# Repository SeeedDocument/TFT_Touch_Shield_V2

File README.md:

# 2.8TFT Touch Shield
---
SKU: 104030004

Wiki Link: [wiki.seeed.cc](wiki.seeed.cc)

Change Log:

- 2016-11-7: create repos by Jeremy (Jeremy.xiao@seeed.cc)

## About Seeed

Seeed is a hardware innovation platform for makers to grow inspirations into differentiating products. By working closely with technology providers of all scale, Seeed provides accessible technologies with quality, speed and supply chain knowledge. When prototypes are ready to iterate, Seeed helps productize 1 to 1,000 pcs using in-house engineering, supply chain management and agile manufacture forces. Seeed also team up with incubators, Chinese tech ecosystem, investors and distribution channels to portal Maker startups beyond.

## Contribution

We warmly welcome contribution to this documentation project. You can do this basically by [forking](https://help.github.com/articles/fork-a-repo), committing modifications and then [pulling requests](https://help.github.com/articles/using-pull-requests) (follow the links above for operating guide). Adding change log and your contact into file header is encouraged. Thanks for your contribution.

LICENSE
-------
Copyright (c) 2008-2016 Seeed Development Limited (www.seeedstudio.com / www.seeed.cc)

### Documents and Images
</a><br />
This work (product documents and associated images) are licensed under a <a rel="license" href="http://creativecommons.org/licenses/by-sa/4.0/">Creative Commons Attribution-ShareAlike 4.0 International License</a>. 

### Software Library
All demo software, code examples embedded in the document and any software libraray provided with the product document are licensed under [MIT License](https://github.com/SeeedDoc/WikiMigrationSync/blob/master/MIT_LICENSE "MIT LICENSE") unless otherwise specified.

### Thirdparty content
The resources provided with the product documents also contains datasheets, software examples and other content copyrighted by 3rd party authors and companies. All such items are copyright of respective owners. The use of such items are governed by their respective licenses.

All trademarks are the property of their respective owners.

### To Contact

Write to us at  with subject line "Wiki". Thanks

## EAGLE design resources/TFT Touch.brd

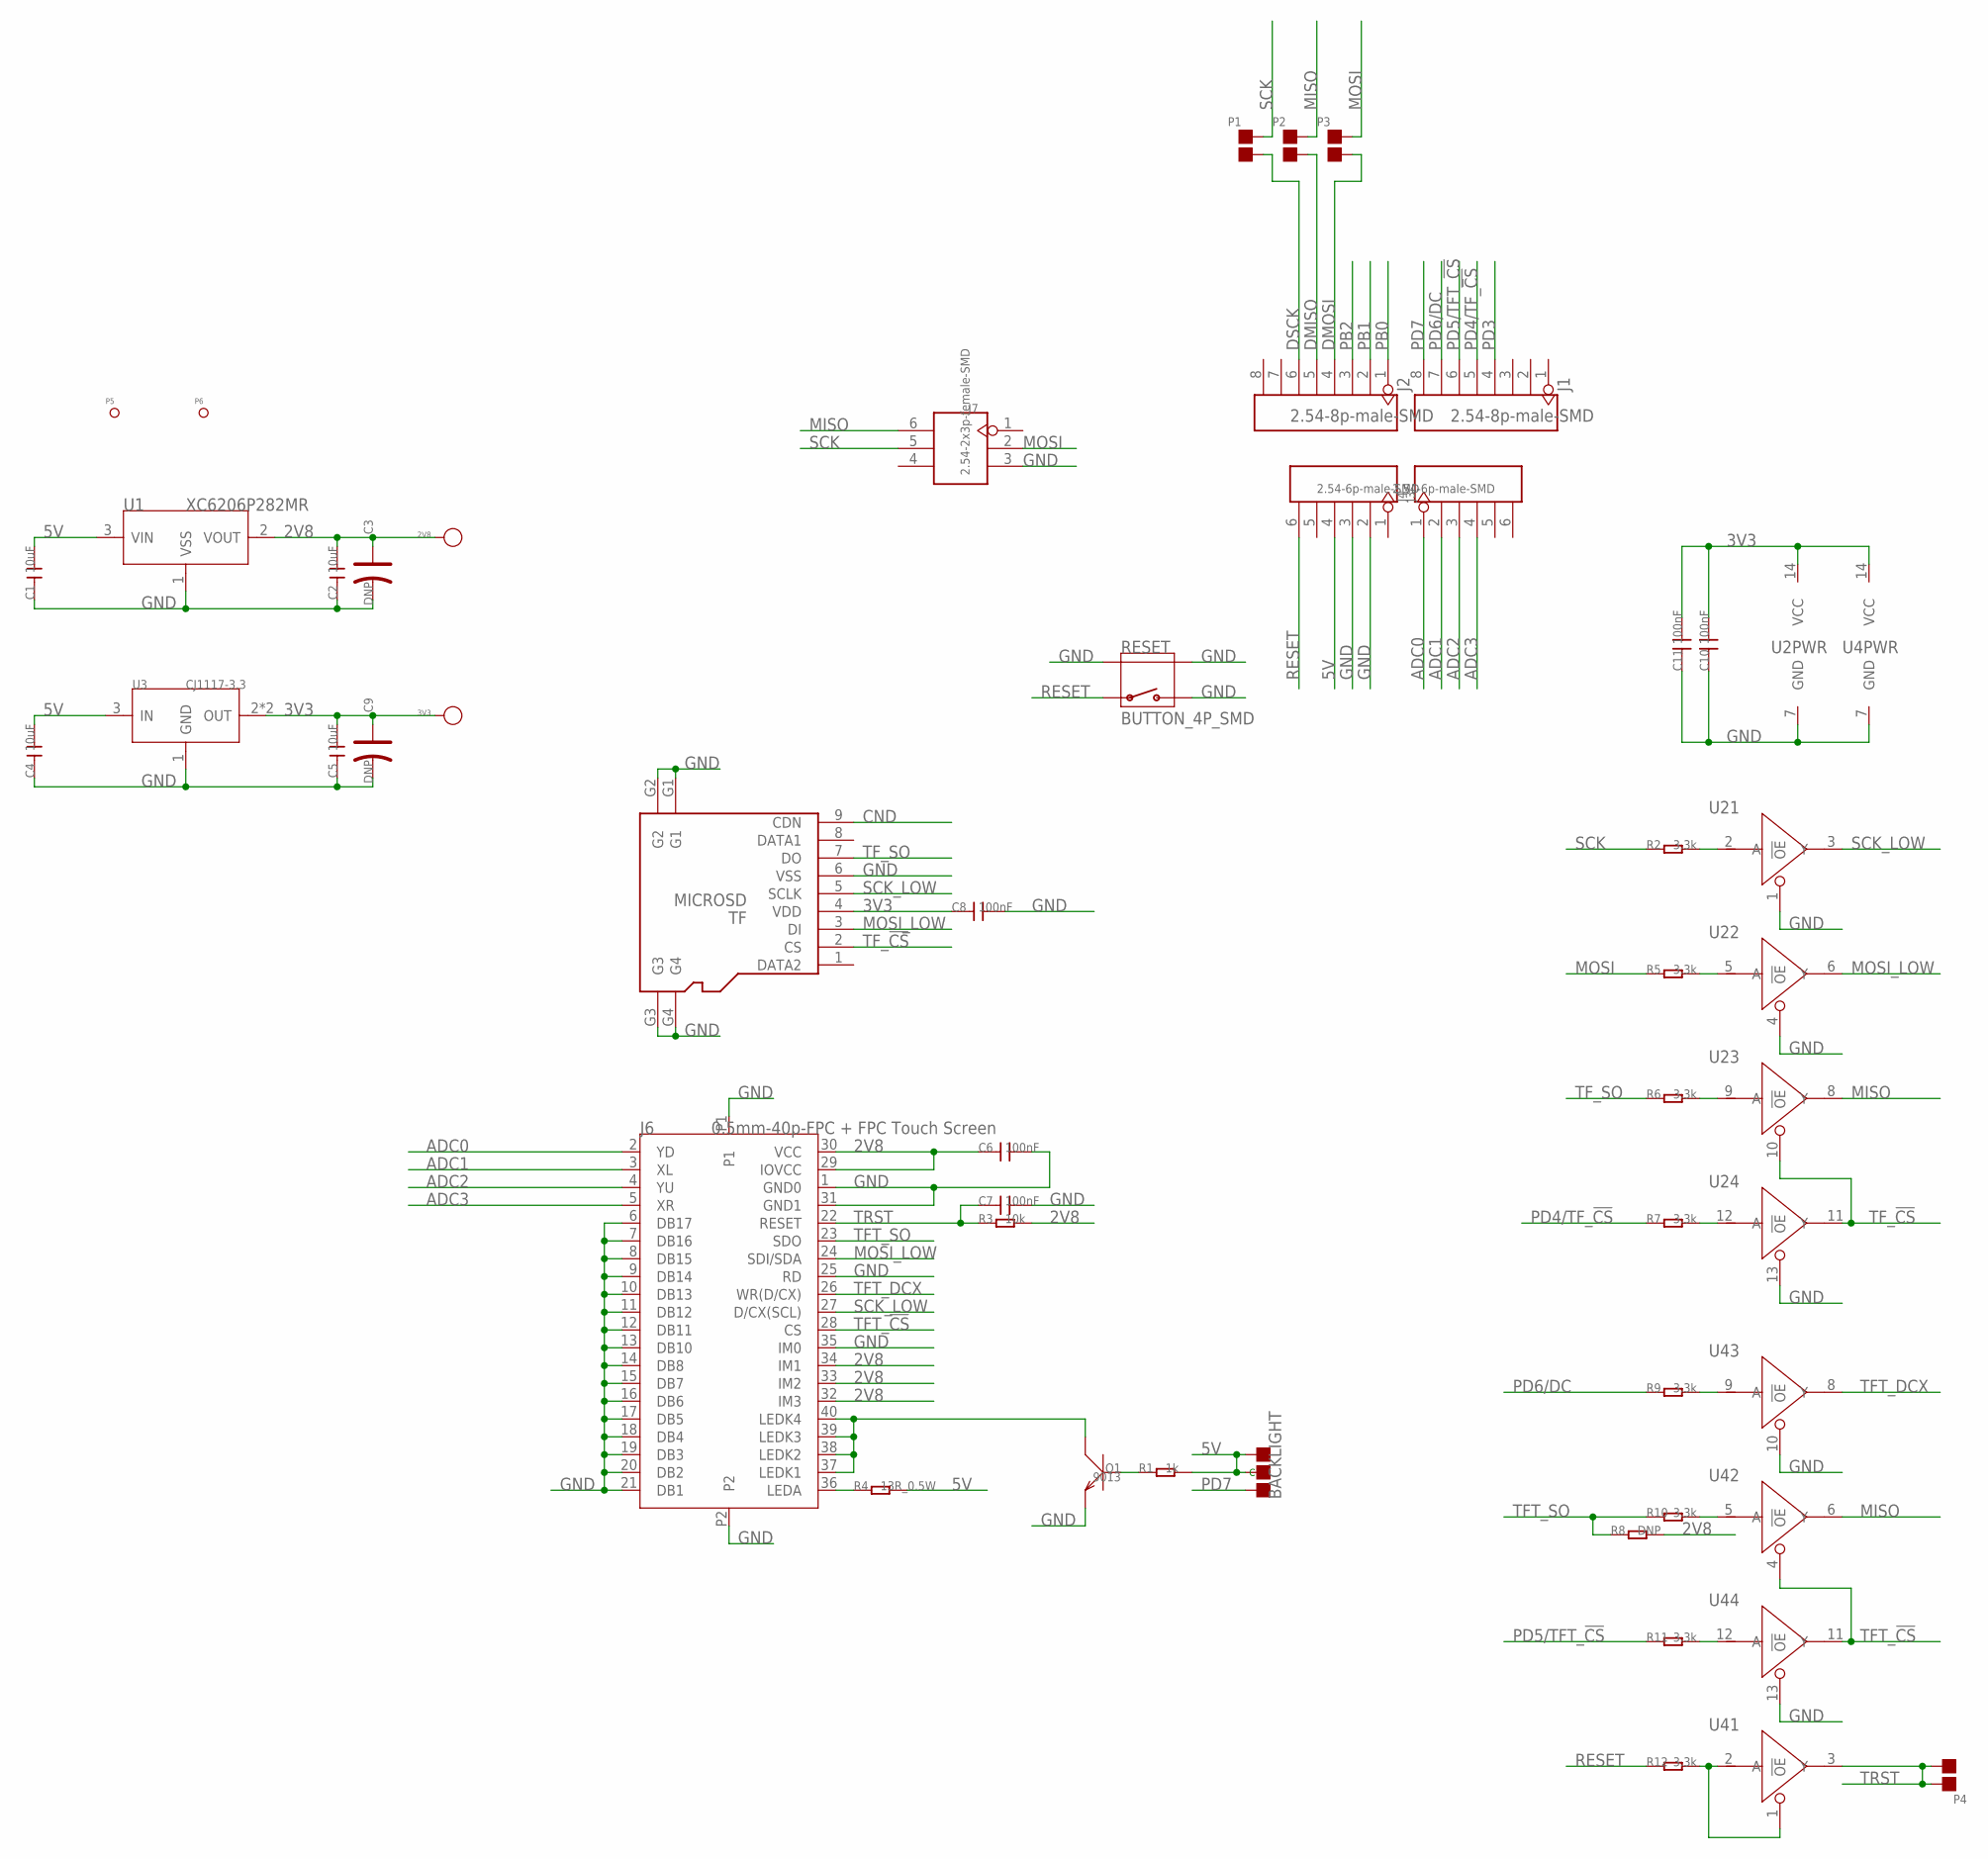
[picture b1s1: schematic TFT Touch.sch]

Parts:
2V8, 3V3: PAD-TEST-POINT-CIRCLE'4545'; TP_4545
BACKLIGHT: DNP; 3P-SMD-4.1X1.5
C1, C2, C4, C5: 10uF; C0805
C3, C9: DNP; AVX-A
C6, C7, C8, C10, C11: 100nF; 0603@1
J1, J2: 2.54-8p-male-SMD; 8P-2.54-SMD
J3, J4: 2.54-6p-male-SMD; 6P-2.54-SMD
J6: 0.5mm-40p-FPC + FPC Touch Screen; 2.8TFT_FFC
J7: 2.54-2x3p-female-SMD; 2X3P-2.54-SMD
P1, P2, P3, P4: PAD-JUMPER-2P; 2P-SMD-1.78X1.27
P5, P6: PAD-MARK; ROUND-MARK-1.0
Q1: 9013; SOT23
R1: 1k; R0603
R2, R5, R6, R7, R9, R10, R11, R12: 3.3k; R0603
R3: 10k; R0603
R4: 13R_0.5W; R1206
R8: DNP; R0603
RESET: BUTTON_4P_SMD; 4P-SMD-7X3.5X3.5
TF: MICROSD
U1: XC6206P282MR; SOT23
U2, U4: 74VHC125PW; TSSOP14
U3: CJ1117-3.3; SOT-223

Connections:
2V8: 2V8.T, C2.2, C3.+, C6.1, J6.29 (IOVCC), J6.30 (VCC), J6.32 (IM3), J6.33 (IM2), J6.34 (IM1), R3.2, R8.2, U1.2 (VOUT)
3V3: 3V3.T, C5.2, C8.1, C9.+, C10.2, C11.2, TF.4 (VDD), U2.14 (VCC), U3.2 (OUT), U3.TER (OUT), U4.14 (VCC)
5V: BACKLIGHT.00 (L), BACKLIGHT.MM (C), C1.2, C4.2, J4.4, R1.2, R4.2, U1.3 (VIN), U3.3 (IN)
ADC0: J3.1, J6.2 (YD)
ADC1: J3.2, J6.3 (XL)
ADC2: J3.3, J6.4 (YU)
ADC3: J3.4, J6.5 (XR)
CND: TF.9 (CDN)
DMISO: J2.5, P2.1
DMOSI: J2.4, P3.1
DSCK: J2.6, P1.1
GND: C1.1, C2.1, C3.-, C4.1, C5.1, C6.2, C7.2, C8.2, C9.-, C10.1, C11.1, J4.2, J4.3, J6.1 (GND0), J6.6 (DB17), J6.7 (DB16), J6.8 (DB15), J6.9 (DB14), J6.10 (DB13), J6.11 (DB12), J6.12 (DB11), J6.13 (DB10), J6.14 (DB8), J6.15 (DB7), J6.16 (DB6), J6.17 (DB5), J6.18 (DB4), J6.19 (DB3), J6.20 (DB2), J6.21 (DB1), J6.25 (RD), J6.31 (GND1), J6.35 (IM0), J6.P1, J6.P2, J7.3, Q1.2 (E), RESET.2, RESET.S1, RESET.S2, TF.6 (VSS), TF.G1, TF.G2, TF.G3, TF.G4, U1.1 (VSS), U2.1 (!OE), U2.4 (!OE), U2.7 (GND), U2.13 (!OE), U3.1 (GND), U4.7 (GND), U4.10 (!OE), U4.13 (!OE)
MISO: J7.6, P2.2, U2.8 (Y), U4.6 (Y)
MOSI: J7.2, P3.2, R5.1
MOSI_LOW: J6.24 (SDI/SDA), TF.3 (DI), U2.6 (Y)
unnamed: R2.2, U2.2 (A)
unnamed: Q1.1 (B), R1.1
unnamed: J6.37 (LEDK1), J6.38 (LEDK2), J6.39 (LEDK3), J6.40 (LEDK4), Q1.3 (C)
unnamed: R5.2, U2.5 (A)
unnamed: R6.2, U2.9 (A)
unnamed: R11.2, U4.12 (A)
unnamed: R10.2, U4.5 (A)
unnamed: J6.36 (LEDA), R4.1
unnamed: R9.2, U4.9 (A)
unnamed: R7.2, U2.12 (A)
PB0: J2.1
PB1: J2.2
PB2: J2.3
PD3: J1.4
PD4/TF_!CS: J1.5, R7.1
PD5/TFT_!CS: J1.6, R11.1
PD6/DC: J1.7, R9.1
PD7: BACKLIGHT.11 (R), J1.8
RESET: J4.6, R12.1, RESET.1
SCK: J7.5, P1.2, R2.1
SCK_LOW: J6.27 (D/CX(SCL)), TF.5 (SCLK), U2.3 (Y)
TFT_!CS: J6.28 (CS), U4.4 (!OE), U4.11 (Y)
TFT_BUF: R12.2, U4.1 (!OE), U4.2 (A)
TFT_DCX: J6.26 (WR(D/CX)), U4.8 (Y)
TFT_SO: J6.23 (SDO), R8.1, R10.1
TF_!CS: TF.2 (CS), U2.10 (!OE), U2.11 (Y)
TF_SO: R6.1, TF.7 (DO)
TRST: C7.1, J6.22 (RESET), P4.1, P4.2, R3.1, U4.3 (Y)

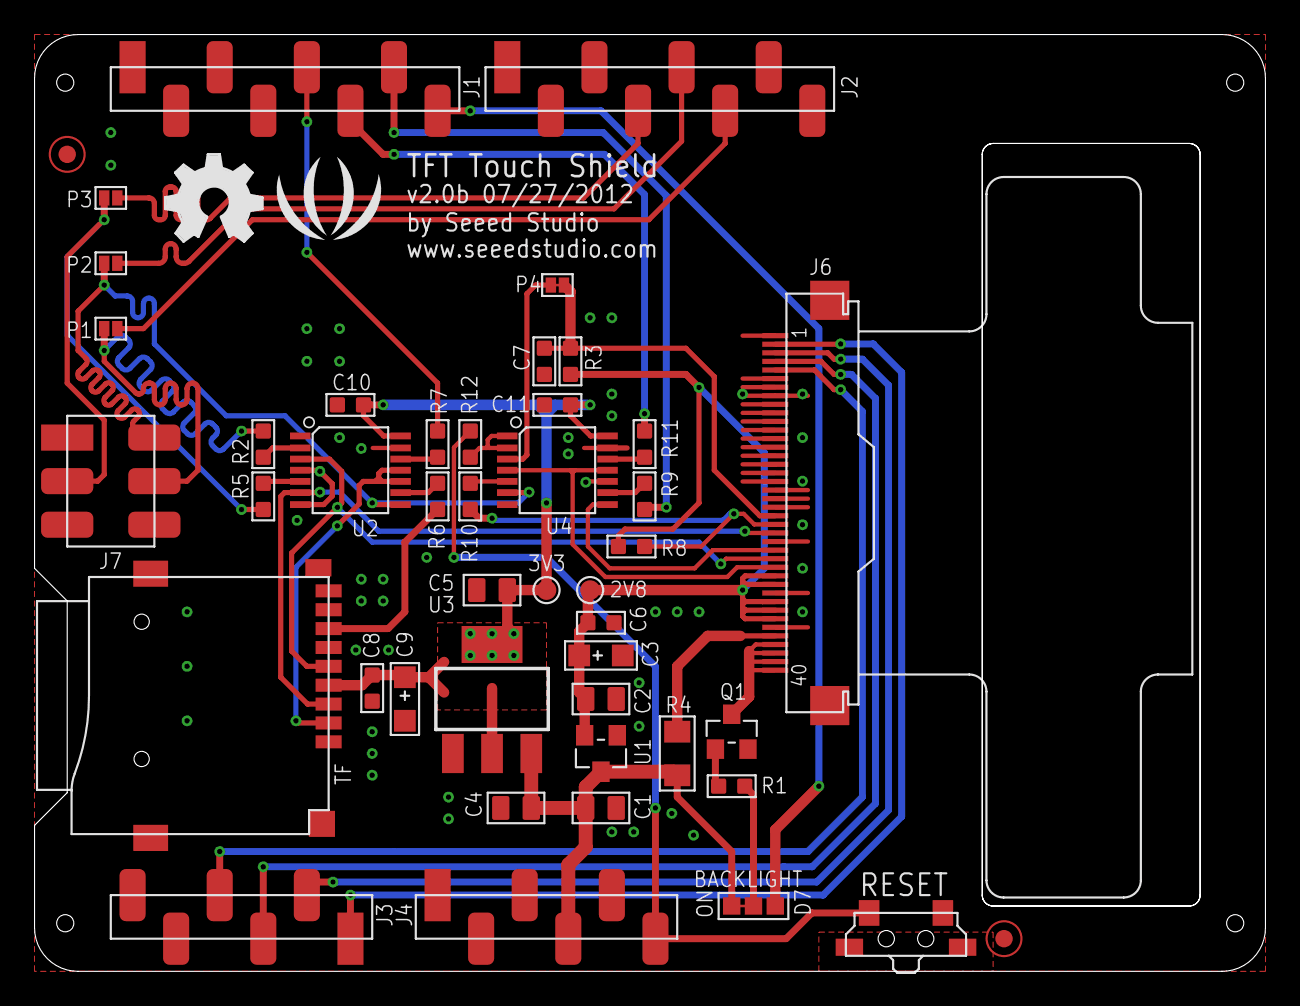
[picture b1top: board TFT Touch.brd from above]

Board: 2 copper layers, 71.8 x 54.6 mm, 47 parts (1 on the bottom side), 38 nets.

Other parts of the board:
U$1: OSHW_FILLX200_NOTEXT
U$2: LOGO_SILK

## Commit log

2016-09-01 add images
2016-09-01 add images and resources
2016-09-01 add library button image
2016-09-01 add backlight image
2016-09-01 update image
2016-09-20 rename
2017-03-28 add shapes example pic
2017-03-28 add PCB pdf file

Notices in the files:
README.md:
CC BY-SA 4.0
